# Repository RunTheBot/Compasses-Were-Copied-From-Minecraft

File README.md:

# Compass from Minecraft
A real compass for Minecraft, which points north in the real world.

## Features
- Points to the North in the real world.
- Looks like a minecraft compass.
- Can be used in any IRL version

## Images

<sub><sup> Got lazy with textures </sup></sub>

<sub><sup> The exploded view is upsidedown, thats why you dont see bolts in the render.</sup></sub>

## BOM

| Name                         | Quantity | Single Unit Price | Total Price | URL/LCSC                                                 | FALSE | Vendor (LCSC unless otheriwse indicated) |   |
|------------------------------|----------|-------------------|-------------|----------------------------------------------------------|-------|------------------------------------------|---|
| Electronics                  |          |                   |             |                                                          | FALSE |                                          |   |
| C5 0603 0.1uF                | 40       |                   |     0.45        | C49678                                                   | FALSE | With My other two projects               |   |
| SK6812MINI                   | 40       |                   | $2.96       | C5149201                                                 | FALSE |                                          |   |
| SEEED XIAO 2040              | 1        |                   | $3.99       | https://www.seeedstudio.com/XIAO-RP2040-v1-0-p-5026.html | FALSE |                                          |   |
| PCB - JLC                    |          |                   | $9.00       |                                                          | FALSE |                                          |   |
| LCSC - Shipping and handling |          |                   | $17.38      |                                                          | FALSE |                                          |   |
| magnometer                   |          |                   | $2.07       | C2654971                                                 | FALSE |                                          |   |
| JLC - Shipping               |          |                   | $10.38      |                                                          | FALSE |                                          |   |
| BSS138 (Level Shifter)       | 1        |                   |     0.45        | C82045                                                   | FALSE | With My other two projects               |   |
| 0603 10K                     | 3        |                   |       0.11      | C98220                                                   | FALSE | With My other two projects               |   |
| seeedstudio shipping         |          |                   | $12.00      |                                                          | FALSE |                                          |   |
|                              |          |                   |             |                                                          | FALSE |                                          |   |
|                              |          |                   |             |                                                          | FALSE |                                          |   |
|                              |          |                   |             |                                                          | FALSE |                                          |   |
|                              |          |                   |             |                                                          | FALSE |                                          |   |
|                              |          |                   |             |                                                          | FALSE |                                          |   |
|                              |          |                   |             |                                                          | FALSE |                                          |   |
|                              |          |                   |             |                                                          | FALSE | With My other two projects               |   |
|                              |          |                   |             |                                                          | FALSE |                                          |   |
|                              |          |                   |             |                                                          | FALSE |                                          |   |
|                              |          |                   |             |                                                          | FALSE |                                          |   |
|                              |          |                   |             |                                                          | FALSE |                                          |   |
|                              |          |                   |             |                                                          | FALSE |                                          |   |
|                              |          |                   |             |                                                          | FALSE |                                          |   |
|                              |          |                   |             |                                                          | FALSE |                                          |   |
|                              |          |                   |             |                                                          | FALSE |                                          |   |
|                              |          |                   |             |                                                          |       |                                          |   |
|                              |          |                   |             |                                                          |       |                                          |   |
|                              |          |                   |             |                                                          |       |                                          |   |
|                              |          |                   |             |                                                          |       |                                          |   |
|                              |          |                   |             |                                                          |       |                                          |   |
|                              |          |                   |             |                                                          |       |                                          |   |
|                              |          |                   |             |                                                          |       |                                          |   |
|                              |          |                   |             |                                                          |       |                                          |   |
|                              |          |                   |             |                                                          |       |                                          |   |
|                              |          |                   |             |                                                          |       |                                          |   |
|                              |          |                   |             | CAD                                                      |       |                                          |   |
|                              |          |                   | $57.78      | USD                                                      |       |                                          |   |
|                              |          |                   | $57.78      | Total - USD                                              |       |                                          |   |

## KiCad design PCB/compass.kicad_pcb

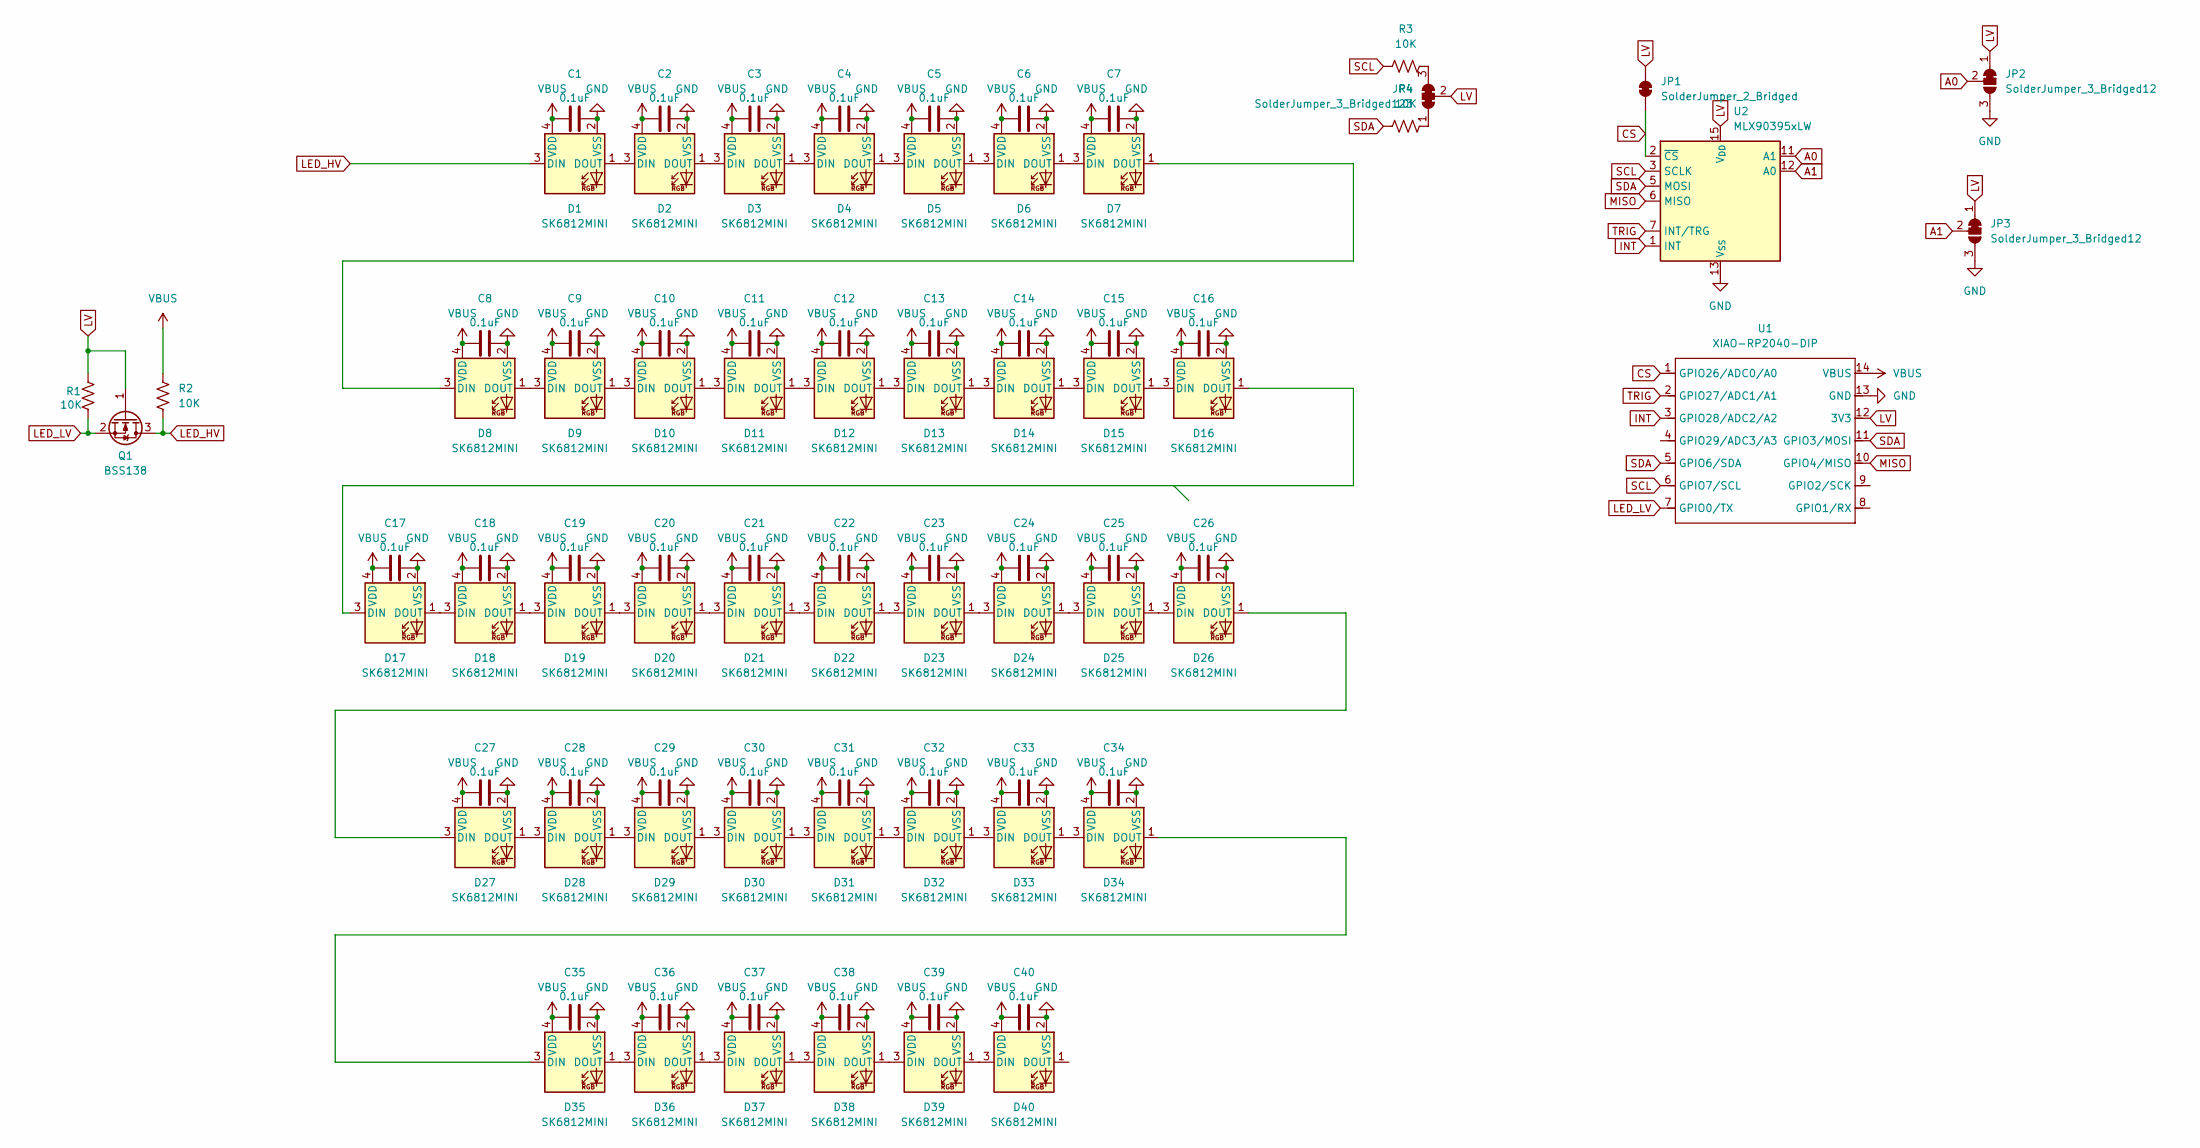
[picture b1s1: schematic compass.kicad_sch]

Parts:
C1, C2, C3, C4, C5, C6, C7, C8, C9, C10, C11, C12, C13, C14, C15, C16, C17, C18, C19, C20, C21, C22, C23, C24, C25, C26, C27, C28, C29, C30, C31, C32, C33, C34, C35, C36, C37, C38, C39, C40: 0.1uF; C_0805_2012Metric_Pad1.18x1.45mm_HandSolder
D1, D2, D3, D4, D5, D6, D7, D8, D9, D10, D11, D12, D13, D14, D15, D16, D17, D18, D19, D20, D21, D22, D23, D24, D25, D26, D27, D28, D29, D30, D31, D32, D33, D34, D35, D36, D37, D38, D39, D40: SK6812MINI; SK6812MINI-E
JP1: SolderJumper_2_Bridged; SolderJumper-2_P1.3mm_Bridged_RoundedPad1.0x1.5mm
JP2, JP3: SolderJumper_3_Bridged12; SolderJumper-3_P1.3mm_Bridged12_RoundedPad1.0x1.5mm
JP4: SolderJumper_3_Bridged123; SolderJumper-3_P1.3mm_Bridged123_RoundedPad1.0x1.5mm_Number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
Q1: BSS138; SOT-23
R1, R2, R3, R4: 10K; R_0603_1608Metric_Pad0.98x0.95mm_HandSolder
U1: XIAO-RP2040-DIP
U2: MLX90395xLW; QFN-16-1EP_3x3mm_P0.5mm_EP1.675x1.675mm

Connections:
A0: JP2.2 (C), U2.11 (A1)
A1: JP3.2 (C), U2.12 (A0)
CS: JP1.1 (A), U1.1 (GPIO26/ADC0/A0), U2.2 (~CS)
GND: C1.2, C2.2, C3.2, C4.2, C5.2, C6.2, C7.2, C8.2, C9.2, C10.2, C11.2, C12.2, C13.2, C14.2, C15.2, C16.2, C17.2, C18.2, C19.2, C20.2, C21.2, C22.2, C23.2, C24.2, C25.2, C26.2, C27.2, C28.2, C29.2, C30.2, C31.2, C32.2, C33.2, C34.2, C35.2, C36.2, C37.2, C38.2, C39.2, C40.2, D1.2 (VSS), D2.2 (VSS), D3.2 (VSS), D4.2 (VSS), D5.2 (VSS), D6.2 (VSS), D7.2 (VSS), D8.2 (VSS), D9.2 (VSS), D10.2 (VSS), D11.2 (VSS), D12.2 (VSS), D13.2 (VSS), D14.2 (VSS), D15.2 (VSS), D16.2 (VSS), D17.2 (VSS), D18.2 (VSS), D19.2 (VSS), D20.2 (VSS), D21.2 (VSS), D22.2 (VSS), D23.2 (VSS), D24.2 (VSS), D25.2 (VSS), D26.2 (VSS), D27.2 (VSS), D28.2 (VSS), D29.2 (VSS), D30.2 (VSS), D31.2 (VSS), D32.2 (VSS), D33.2 (VSS), D34.2 (VSS), D35.2 (VSS), D36.2 (VSS), D37.2 (VSS), D38.2 (VSS), D39.2 (VSS), D40.2 (VSS), JP2.3 (B), JP3.3 (B), U1.13 (GND), U2.4 (V_{SS}), U2.8 (V_{SS}), U2.9 (V_{SS}), U2.10 (V_{SS}), U2.13 (V_{SS}), U2.14 (V_{SS}), U2.16 (V_{SS}), U2.17 (V_{SS})
INT: U1.3 (GPIO28/ADC2/A2), U2.1 (INT)
LED_HV: D1.3 (DIN), Q1.3 (D), R2.2
LED_LV: Q1.2 (S), R1.2, U1.7 (GPIO0/TX)
LV: JP1.2 (B), JP2.1 (A), JP3.1 (A), JP4.2 (C), Q1.1 (G), R1.1, U1.12 (3V3), U2.15 (V_{DD})
MISO: U1.10 (GPIO4/MISO), U2.6 (MISO)
unnamed: D1.1 (DOUT), D2.3 (DIN)
unnamed: D2.1 (DOUT), D3.3 (DIN)
unnamed: D3.1 (DOUT), D4.3 (DIN)
unnamed: D4.1 (DOUT), D5.3 (DIN)
unnamed: D5.1 (DOUT), D6.3 (DIN)
unnamed: D6.1 (DOUT), D7.3 (DIN)
unnamed: D7.1 (DOUT), D8.3 (DIN)
unnamed: D8.1 (DOUT), D9.3 (DIN)
unnamed: D9.1 (DOUT), D10.3 (DIN)
unnamed: D10.1 (DOUT), D11.3 (DIN)
unnamed: D11.1 (DOUT), D12.3 (DIN)
unnamed: D12.1 (DOUT), D13.3 (DIN)
unnamed: D13.1 (DOUT), D14.3 (DIN)
unnamed: D14.1 (DOUT), D15.3 (DIN)
unnamed: D15.1 (DOUT), D16.3 (DIN)
unnamed: D16.1 (DOUT), D17.3 (DIN)
unnamed: D17.1 (DOUT), D18.3 (DIN)
unnamed: D18.1 (DOUT), D19.3 (DIN)
unnamed: D19.1 (DOUT), D20.3 (DIN)
unnamed: D20.1 (DOUT), D21.3 (DIN)
unnamed: D21.1 (DOUT), D22.3 (DIN)
unnamed: D22.1 (DOUT), D23.3 (DIN)
unnamed: D23.1 (DOUT), D24.3 (DIN)
unnamed: D24.1 (DOUT), D25.3 (DIN)
unnamed: D25.1 (DOUT), D26.3 (DIN)
unnamed: D26.1 (DOUT), D27.3 (DIN)
unnamed: D27.1 (DOUT), D28.3 (DIN)
unnamed: D28.1 (DOUT), D29.3 (DIN)
unnamed: D29.1 (DOUT), D30.3 (DIN)
unnamed: D30.1 (DOUT), D31.3 (DIN)
unnamed: D31.1 (DOUT), D32.3 (DIN)
unnamed: D32.1 (DOUT), D33.3 (DIN)
unnamed: D33.1 (DOUT), D34.3 (DIN)
unnamed: D34.1 (DOUT), D35.3 (DIN)
unnamed: D35.1 (DOUT), D36.3 (DIN)
unnamed: D36.1 (DOUT), D37.3 (DIN)
unnamed: D37.1 (DOUT), D38.3 (DIN)
unnamed: D38.1 (DOUT), D39.3 (DIN)
unnamed: D39.1 (DOUT), D40.3 (DIN)
unnamed: JP4.1 (A), R4.2
unnamed: JP4.3 (B), R3.2
SCL: R3.1, U1.6 (GPIO7/SCL), U2.3 (SCLK)
SDA: R4.1, U1.5 (GPIO6/SDA), U1.11 (GPIO3/MOSI), U2.5 (MOSI)
TRIG: U1.2 (GPIO27/ADC1/A1), U2.7 (INT/TRG)
VBUS: C1.1, C2.1, C3.1, C4.1, C5.1, C6.1, C7.1, C8.1, C9.1, C10.1, C11.1, C12.1, C13.1, C14.1, C15.1, C16.1, C17.1, C18.1, C19.1, C20.1, C21.1, C22.1, C23.1, C24.1, C25.1, C26.1, C27.1, C28.1, C29.1, C30.1, C31.1, C32.1, C33.1, C34.1, C35.1, C36.1, C37.1, C38.1, C39.1, C40.1, D1.4 (VDD), D2.4 (VDD), D3.4 (VDD), D4.4 (VDD), D5.4 (VDD), D6.4 (VDD), D7.4 (VDD), D8.4 (VDD), D9.4 (VDD), D10.4 (VDD), D11.4 (VDD), D12.4 (VDD), D13.4 (VDD), D14.4 (VDD), D15.4 (VDD), D16.4 (VDD), D17.4 (VDD), D18.4 (VDD), D19.4 (VDD), D20.4 (VDD), D21.4 (VDD), D22.4 (VDD), D23.4 (VDD), D24.4 (VDD), D25.4 (VDD), D26.4 (VDD), D27.4 (VDD), D28.4 (VDD), D29.4 (VDD), D30.4 (VDD), D31.4 (VDD), D32.4 (VDD), D33.4 (VDD), D34.4 (VDD), D35.4 (VDD), D36.4 (VDD), D37.4 (VDD), D38.4 (VDD), D39.4 (VDD), D40.4 (VDD), R2.1, U1.14 (VBUS)

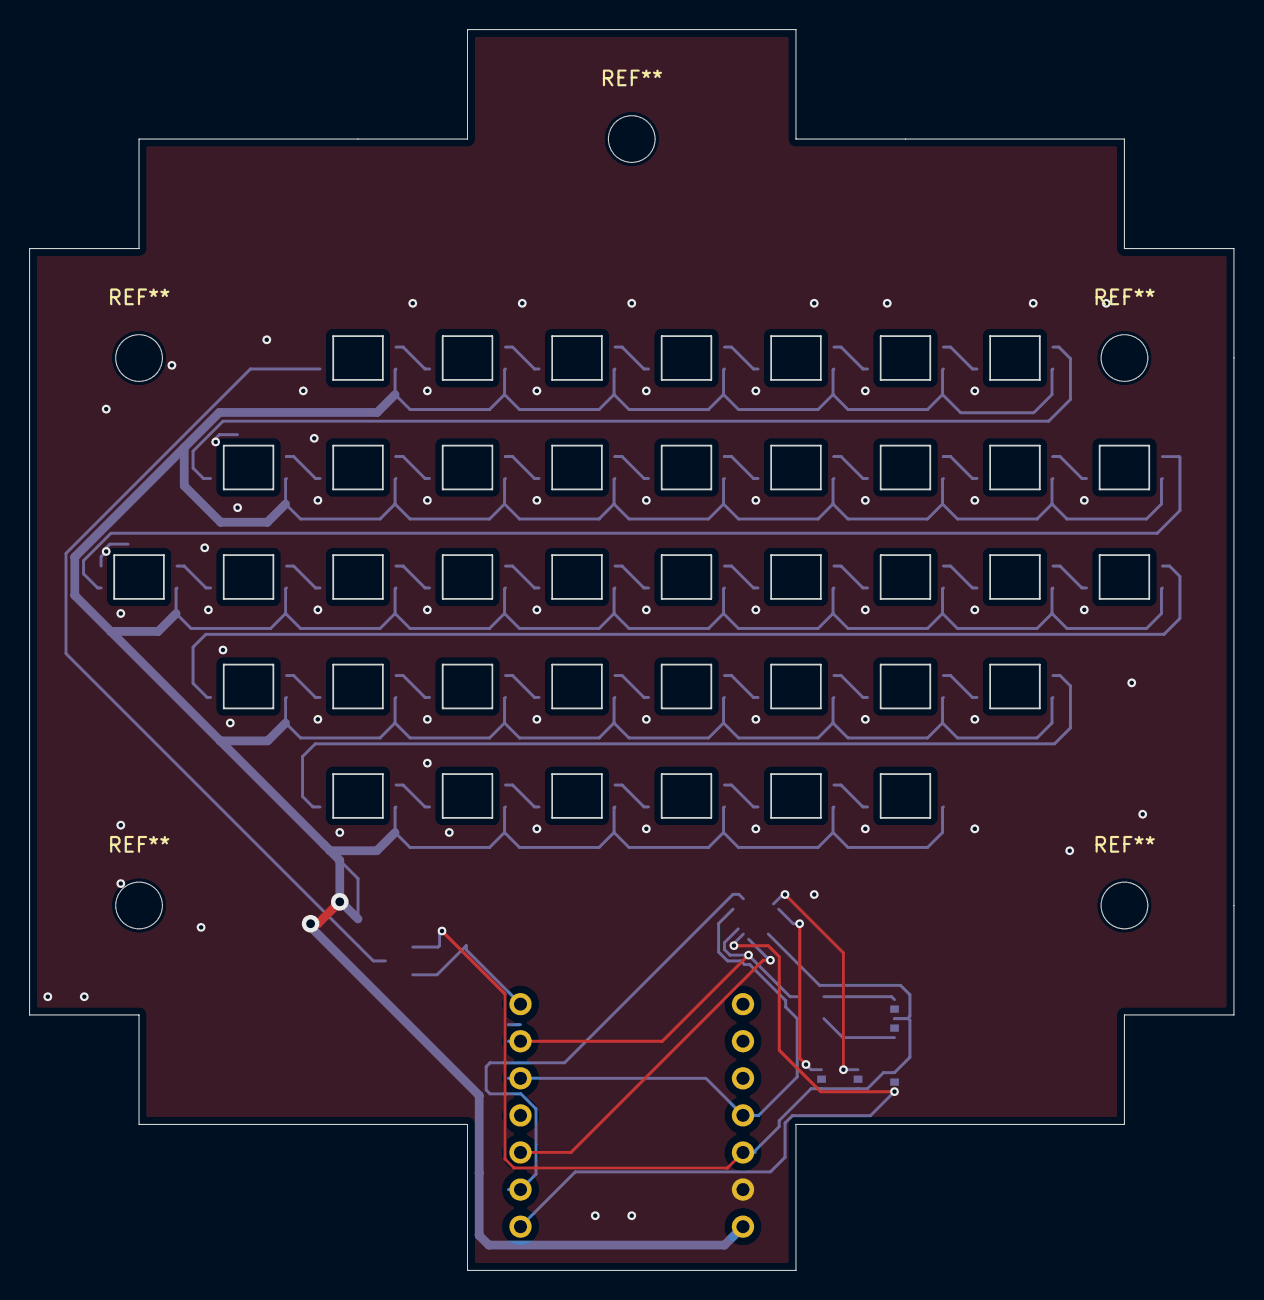
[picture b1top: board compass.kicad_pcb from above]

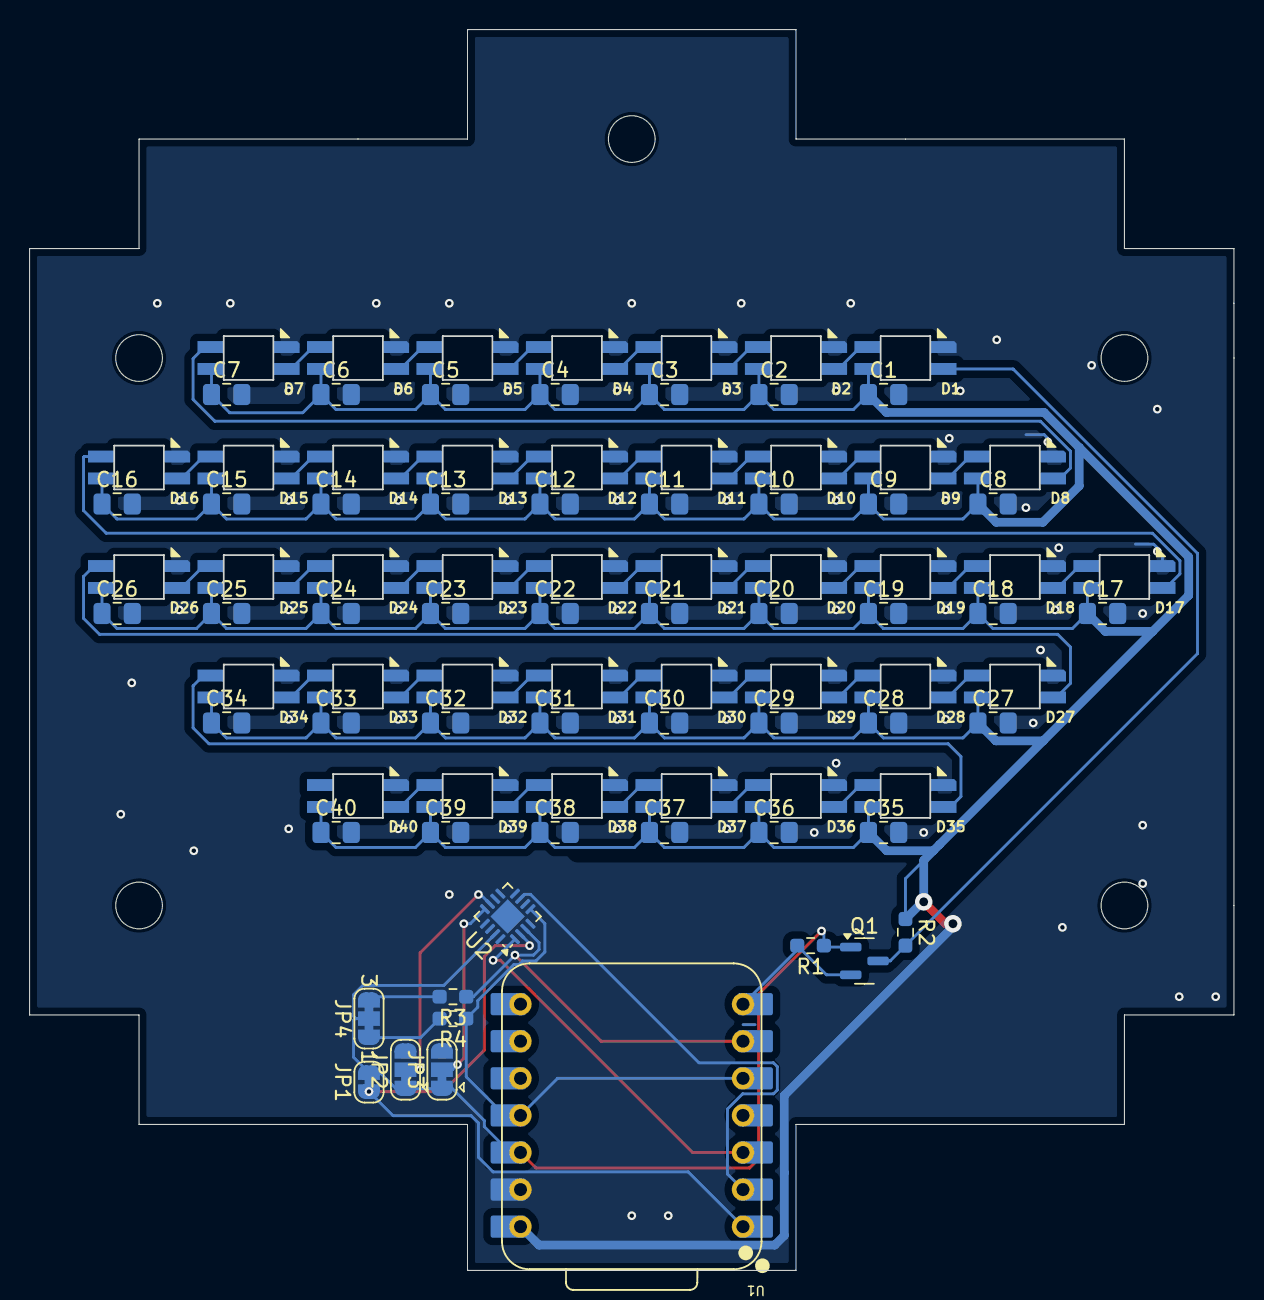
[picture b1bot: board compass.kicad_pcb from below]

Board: 2 copper layers, 82.5 x 85.0 mm, 91 parts (91 on the bottom side), 54 nets.

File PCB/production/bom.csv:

Designator,Footprint,Quantity,Value,LCSC Part #
"C1, C10, C11, C12, C13, C14, C15, C16, C17, C18, C19, C2, C20, C21, C22, C23, C24, C25, C26, C27, C28, C29, C3, C30, C31, C32, C33, C34, C35, C36, C37, C38, C39, C4, C40, C5, C6, C7, C8, C9",0805,40,0.1uF,
"D1, D10, D11, D12, D13, D14, D15, D16, D17, D18, D19, D2, D20, D21, D22, D23, D24, D25, D26, D27, D28, D29, D3, D30, D31, D32, D33, D34, D35, D36, D37, D38, D39, D4, D40, D5, D6, D7, D8, D9",SK6812MINI-E,40,SK6812MINI,
Q1,SOT-23,1,BSS138,
"R1, R2",0603,2,10K,
U1,XIAO-RP2040-DIP,1,XIAO-RP2040-DIP,

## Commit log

2025-06-26 asdasd
2025-06-26 bruh
2025-06-26 Add BOM section with detailed component list and pricing
